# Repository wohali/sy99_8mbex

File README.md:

Yamaha SY99 8MB expansion board

v1.0 - Fabricated July/August 2018 - has issues, do not use

v1.1 - Fabricated September 2018 - all good!

Copyright 2018 Joan Sarah Touzet

License: CC BY-SA 3.0

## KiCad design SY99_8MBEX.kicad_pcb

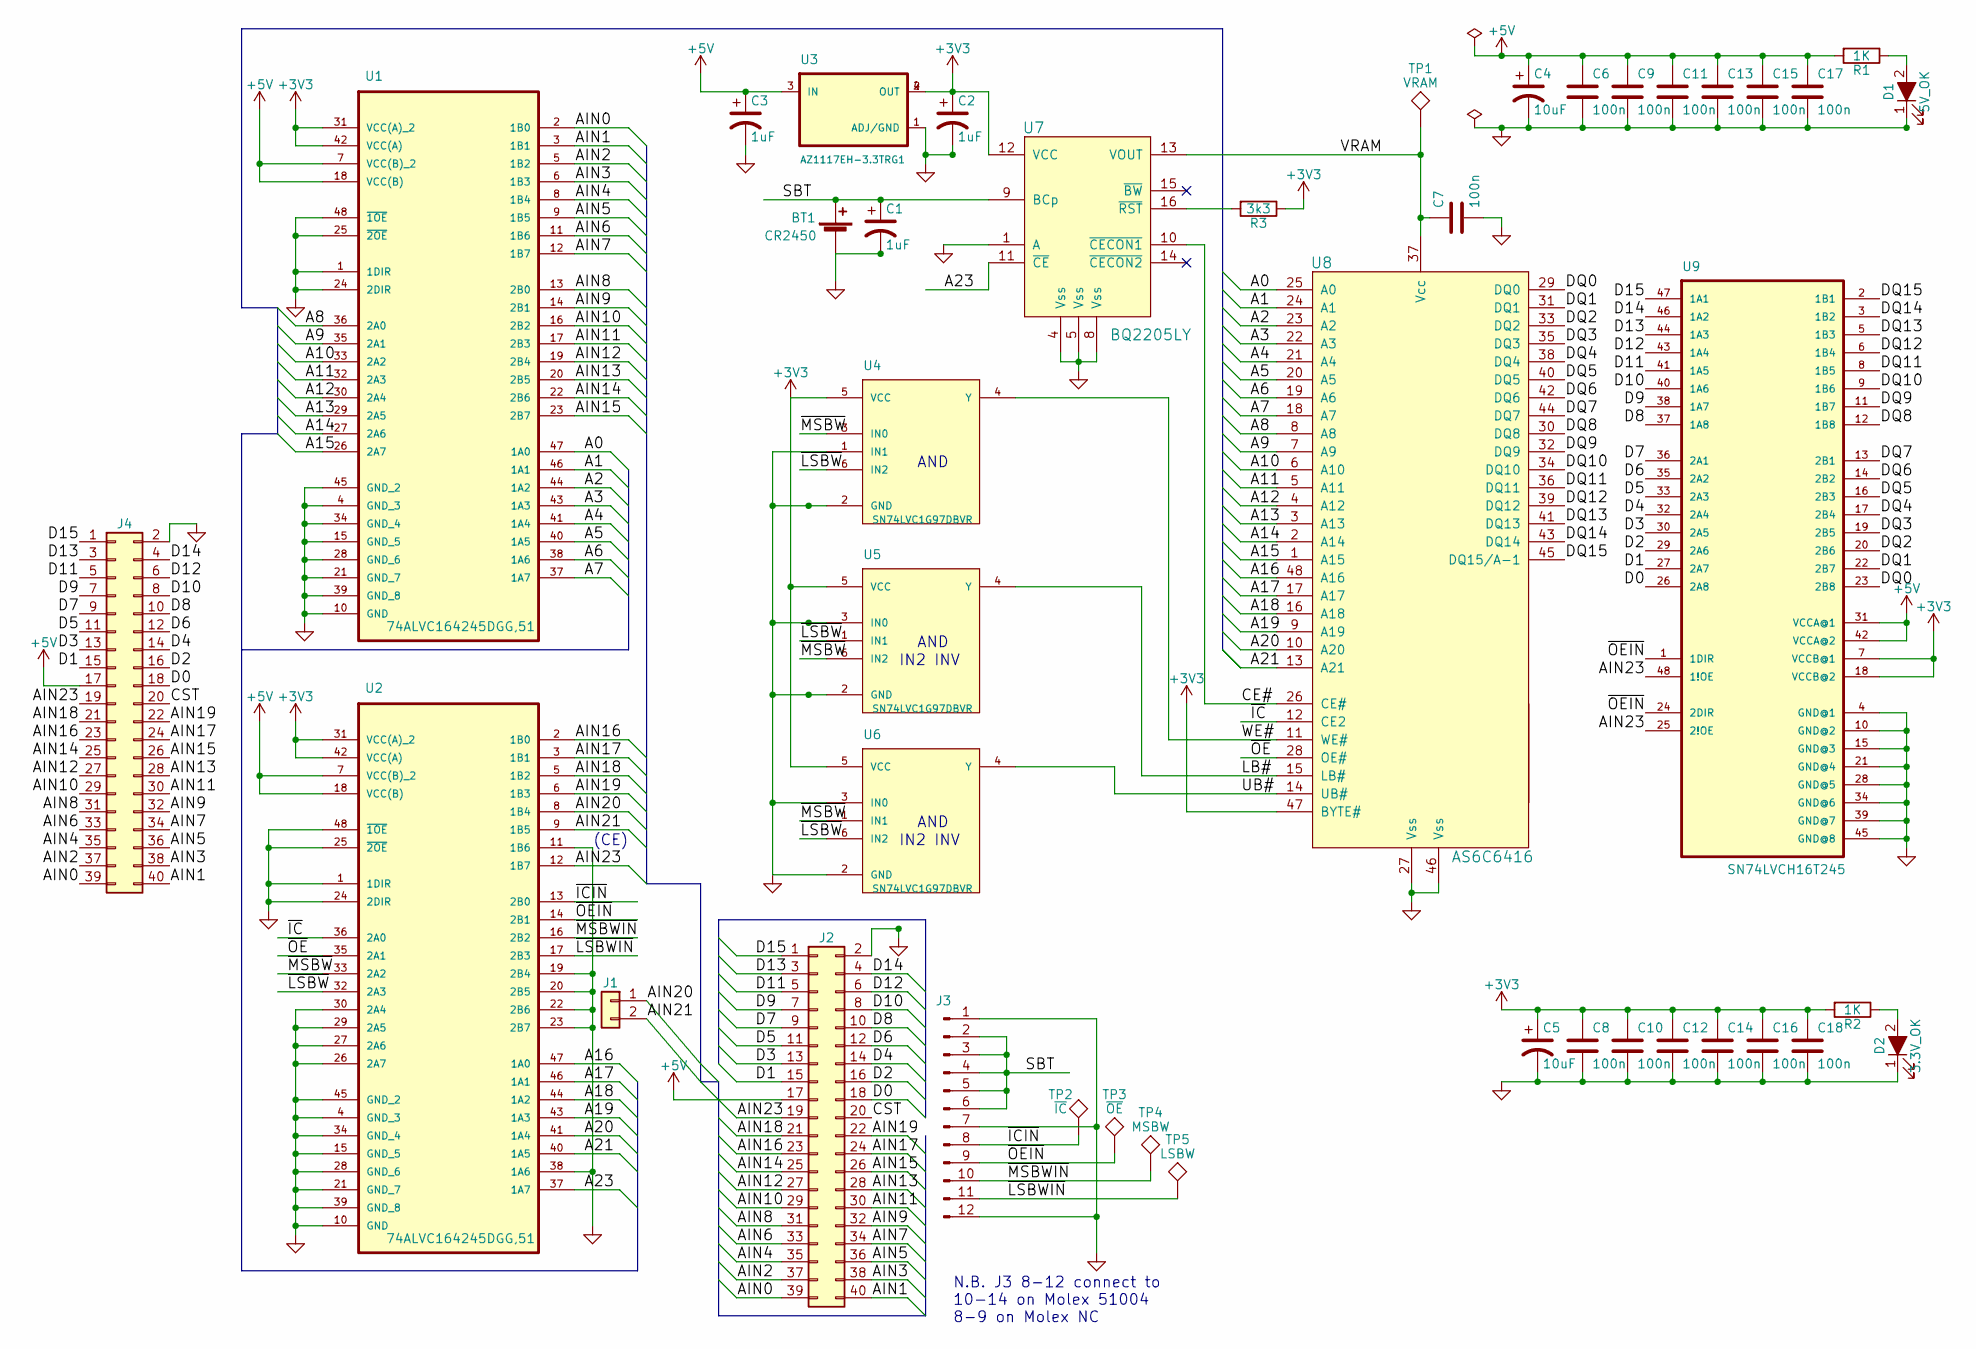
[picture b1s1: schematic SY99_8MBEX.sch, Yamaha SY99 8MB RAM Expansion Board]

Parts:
BT1: CR2450; Battery_Holder_Coin_2032_BS-7
C1, C2, C3: 1uF; CP_Tantalum_Case-A_EIA-3216-18_Reflow
C4, C5: 10uF; CP_Tantalum_Case-A_EIA-3216-18_Reflow
C6, C7, C8, C9, C10, C11, C12, C13, C14, C15, C16, C17, C18: 100n; C_0805_HandSoldering
D1: 5V_OK; LED_D5.0mm
D2: 3.3V_OK; LED_D5.0mm
J1: Conn_01x02; Pin_Header_Angled_1x02_Pitch2.54mm
J2: Conn_02x20_Odd_Even; Socket_Strip_Straight_2x20_Pitch2.54mm_10.30Wide_SMD
J3: Conn_01x12_Male; Pin_Header_Straight_1x12_Pitch2.54mm
J4: Conn_02x20_Odd_Even; Pin_Header_Straight_2x20_Pitch2.54mm_10.30Wide_SMD
R1, R2: 1K; R_0805_HandSoldering
R3: 3k3; R_0805_HandSoldering
TP1: VRAM; PINTST
TP2: ~IC; PINTST
TP3: ~OE; PINTST
TP4: MSBW; PINTST
TP5: LSBW; PINTST
U1, U2: 74ALVC164245DGG,51; SOP50P810X120-48N
U3: AZ1117EH-3.3TRG1; SOT230P700X180-4N
U4, U5, U6: SN74LVC1G97DBVR; SOT95P280X145-6N
U7: BQ2205LY; SOP65P640X120-16N
U8: AS6C6416; TSOP48
U9: SN74LVCH16T245; TSSOP48

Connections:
+3V3: C2.1, C5.1, C8.1, C10.1, C12.1, C14.1, C16.1, C18.1, R2.2, R3.1, U1.31 (VCC(A)_2), U1.42 (VCC(A)), U2.31 (VCC(A)_2), U2.42 (VCC(A)), U3.2 (OUT), U3.4 (OUT), U4.5 (VCC), U5.5 (VCC), U6.5 (VCC), U7.12 (VCC), U8.47 (BYTE#), U9.7 (VCCB@1), U9.18 (VCCB@2)
+5V: C3.1, C4.1, C6.1, C9.1, C11.1, C13.1, C15.1, C17.1, J2.17, J4.17, R1.2, U1.7 (VCC(B)_2), U1.18 (VCC(B)), U2.7 (VCC(B)_2), U2.18 (VCC(B)), U3.3 (IN), U9.31 (VCCA@1), U9.42 (VCCA@2)
/A0: U1.47 (1A0), U8.25 (A0)
/A1: U1.46 (1A1), U8.24 (A1)
/A2: U1.44 (1A2), U8.23 (A2)
/A3: U1.43 (1A3), U8.22 (A3)
/A4: U1.41 (1A4), U8.21 (A4)
/A5: U1.40 (1A5), U8.20 (A5)
/A6: U1.38 (1A6), U8.19 (A6)
/A7: U1.37 (1A7), U8.18 (A7)
/A8: U1.36 (2A0), U8.8 (A8)
/A9: U1.35 (2A1), U8.7 (A9)
/A10: U1.33 (2A2), U8.6 (A10)
/A11: U1.32 (2A3), U8.5 (A11)
/A12: U1.30 (2A4), U8.4 (A12)
/A13: U1.29 (2A5), U8.3 (A13)
/A14: U1.27 (2A6), U8.2 (A14)
/A15: U1.26 (2A7), U8.1 (A15)
/A16: U2.47 (1A0), U8.48 (A16)
/A17: U2.46 (1A1), U8.17 (A17)
/A18: U2.44 (1A2), U8.16 (A18)
/A19: U2.43 (1A3), U8.9 (A19)
/A20: U2.41 (1A4), U8.10 (A20)
/A21: U2.40 (1A5), U8.13 (A21)
/A23: U2.37 (1A7), U7.11 (~CE)
/AIN0: J2.39, J4.39, U1.2 (1B0)
/AIN1: J2.40, J4.40, U1.3 (1B1)
/AIN2: J2.37, J4.37, U1.5 (1B2)
/AIN3: J2.38, J4.38, U1.6 (1B3)
/AIN4: J2.35, J4.35, U1.8 (1B4)
/AIN5: J2.36, J4.36, U1.9 (1B5)
/AIN6: J2.33, J4.33, U1.11 (1B6)
/AIN7: J2.34, J4.34, U1.12 (1B7)
/AIN8: J2.31, J4.31, U1.13 (2B0)
/AIN9: J2.32, J4.32, U1.14 (2B1)
/AIN10: J2.29, J4.29, U1.16 (2B2)
/AIN11: J2.30, J4.30, U1.17 (2B3)
/AIN12: J2.27, J4.27, U1.19 (2B4)
/AIN13: J2.28, J4.28, U1.20 (2B5)
/AIN14: J2.25, J4.25, U1.22 (2B6)
/AIN15: J2.26, J4.26, U1.23 (2B7)
/AIN16: J2.23, J4.23, U2.2 (1B0)
/AIN17: J2.24, J4.24, U2.3 (1B1)
/AIN18: J2.21, J4.21, U2.5 (1B2)
/AIN19: J2.22, J4.22, U2.6 (1B3)
/AIN20: J1.1, U2.8 (1B4)
/AIN21: J1.2, U2.9 (1B5)
/AIN23: J2.19, J4.19, U2.12 (1B7), U9.25 (2!OE), U9.48 (1!OE)
/CE#: U7.10 (~CECON1), U8.26 (CE#)
/CST: J2.20, J4.20
/D0: J2.18, J4.18, U9.26 (2A8)
/D1: J2.15, J4.15, U9.27 (2A7)
/D2: J2.16, J4.16, U9.29 (2A6)
/D3: J2.13, J4.13, U9.30 (2A5)
/D4: J2.14, J4.14, U9.32 (2A4)
/D5: J2.11, J4.11, U9.33 (2A3)
/D6: J2.12, J4.12, U9.35 (2A2)
/D7: J2.9, J4.9, U9.36 (2A1)
/D8: J2.10, J4.10, U9.37 (1A8)
/D9: J2.7, J4.7, U9.38 (1A7)
/D10: J2.8, J4.8, U9.40 (1A6)
/D11: J2.5, J4.5, U9.41 (1A5)
/D12: J2.6, J4.6, U9.43 (1A4)
/D13: J2.3, J4.3, U9.44 (1A3)
/D14: J2.4, J4.4, U9.46 (1A2)
/D15: J2.1, J4.1, U9.47 (1A1)
/DQ0: U8.29 (DQ0), U9.23 (2B8)
/DQ1: U8.31 (DQ1), U9.22 (2B7)
/DQ2: U8.33 (DQ2), U9.20 (2B6)
/DQ3: U8.35 (DQ3), U9.19 (2B5)
/DQ4: U8.38 (DQ4), U9.17 (2B4)
/DQ5: U8.40 (DQ5), U9.16 (2B3)
/DQ6: U8.42 (DQ6), U9.14 (2B2)
/DQ7: U8.44 (DQ7), U9.13 (2B1)
/DQ8: U8.30 (DQ8), U9.12 (1B8)
/DQ9: U8.32 (DQ9), U9.11 (1B7)
/DQ10: U8.34 (DQ10), U9.9 (1B6)
/DQ11: U8.36 (DQ11), U9.8 (1B5)
/DQ12: U8.39 (DQ12), U9.6 (1B4)
/DQ13: U8.41 (DQ13), U9.5 (1B3)
/DQ14: U8.43 (DQ14), U9.3 (1B2)
/DQ15: U8.45 (DQ15/A-1), U9.2 (1B1)
/LB#: U5.4 (Y), U8.15 (LB#)
/SBT: BT1.1 (+), C1.1, J3.2, J3.3, J3.4, J3.5, J3.6, U7.9 (BCp)
/UB#: U6.4 (Y), U8.14 (UB#)
/VRAM: C7.1, TP1.1, U7.13 (VOUT), U8.37 (Vcc)
/WE#: U4.4 (Y), U8.11 (WE#)
/~IC: U2.36 (2A0), U8.12 (CE2)
/~ICIN: J3.8, TP2.1, U2.13 (2B0)
/~LSBW: U2.32 (2A3), U4.6 (IN2), U5.1 (IN1), U6.6 (IN2)
/~LSBWIN: J3.11, TP5.1, U2.17 (2B3)
/~MSBW: U2.33 (2A2), U4.3 (IN0), U5.6 (IN2), U6.1 (IN1)
/~MSBWIN: J3.10, TP4.1, U2.16 (2B2)
/~OE: U2.35 (2A1), U8.28 (OE#)
/~OEIN: J3.9, TP3.1, U2.14 (2B1), U9.1 (1DIR), U9.24 (2DIR)
GND: BT1.2 (-), C1.2, C2.2, C3.2, C4.2, C5.2, C6.2, C7.2, C8.2, C9.2, C10.2, C11.2, C12.2, C13.2, C14.2, C15.2, C16.2, C17.2, C18.2, D1.1 (K), D2.1 (K), J2.2, J3.1, J3.7, J3.12, J4.2, U1.1 (1DIR), U1.4 (GND_3), U1.10 (GND), U1.15 (GND_5), U1.21 (GND_7), U1.24 (2DIR), U1.25 (~2OE), U1.28 (GND_6), U1.34 (GND_4), U1.39 (GND_8), U1.45 (GND_2), U1.48 (~1OE), U2.1 (1DIR), U2.4 (GND_3), U2.10 (GND), U2.11 (1B6), U2.15 (GND_5), U2.19 (2B4), U2.20 (2B5), U2.21 (GND_7), U2.22 (2B6), U2.23 (2B7), U2.24 (2DIR), U2.25 (~2OE), U2.26 (2A7), U2.27 (2A6), U2.28 (GND_6), U2.29 (2A5), U2.30 (2A4), U2.34 (GND_4), U2.38 (1A6), U2.39 (GND_8), U2.45 (GND_2), U2.48 (~1OE), U3.1 (ADJ/GND), U4.1 (IN1), U4.2 (GND), U5.2 (GND), U5.3 (IN0), U6.2 (GND), U6.3 (IN0), U7.1 (A), U7.4 (Vss), U7.5 (Vss), U7.8 (Vss), U8.27 (Vss), U8.46 (Vss), U9.4 (GND@1), U9.10 (GND@2), U9.15 (GND@3), U9.21 (GND@4), U9.28 (GND@5), U9.34 (GND@6), U9.39 (GND@7), U9.45 (GND@8)
unnamed: D1.2 (A), R1.1
unnamed: D2.2 (A), R2.1
unnamed: R3.2, U7.16 (~RST)

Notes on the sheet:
(CE)
AND
IN2 INV
N.B. J3 8-12 connect to 10-14 on Molex 51004 8-9 on Molex NC

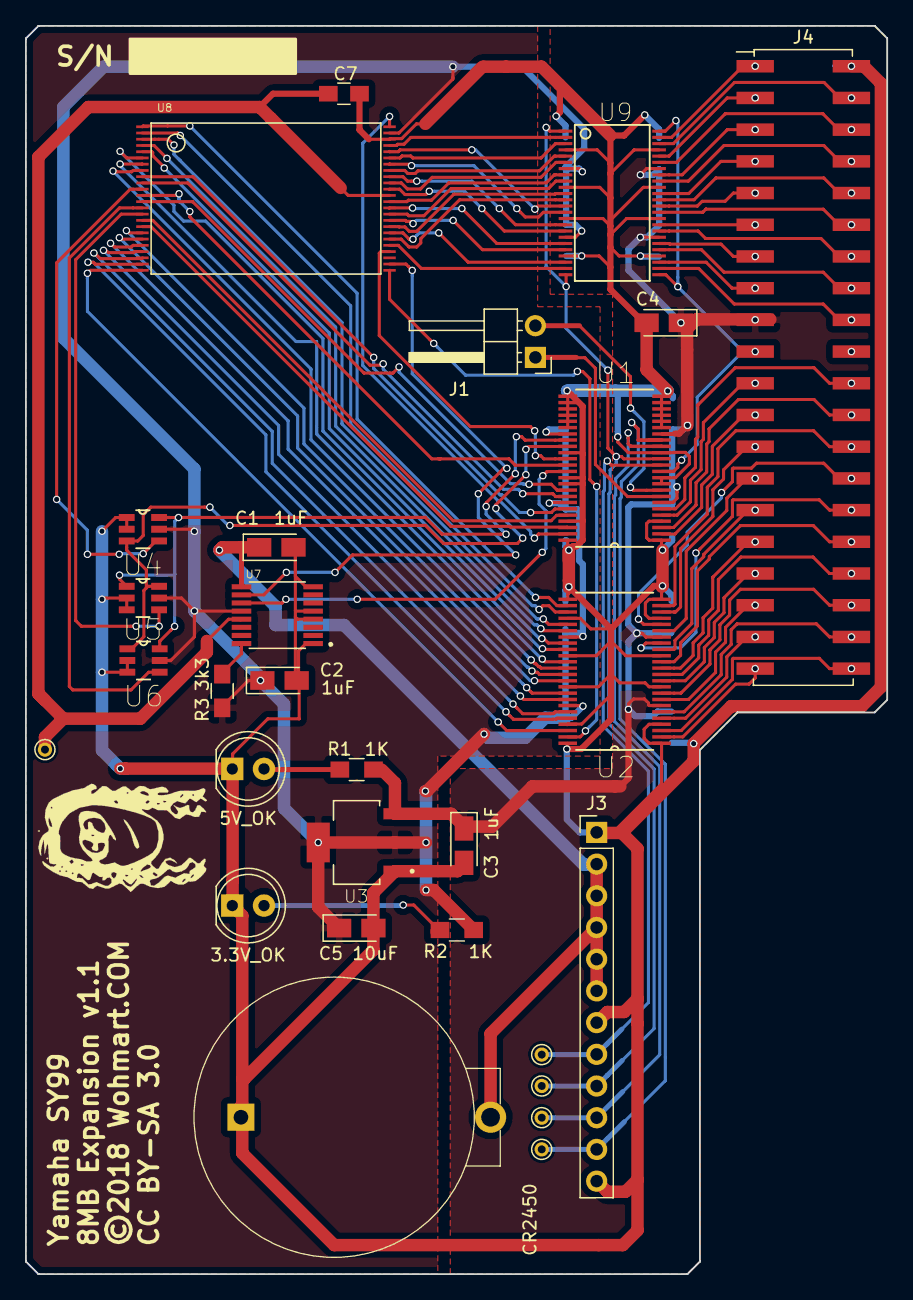
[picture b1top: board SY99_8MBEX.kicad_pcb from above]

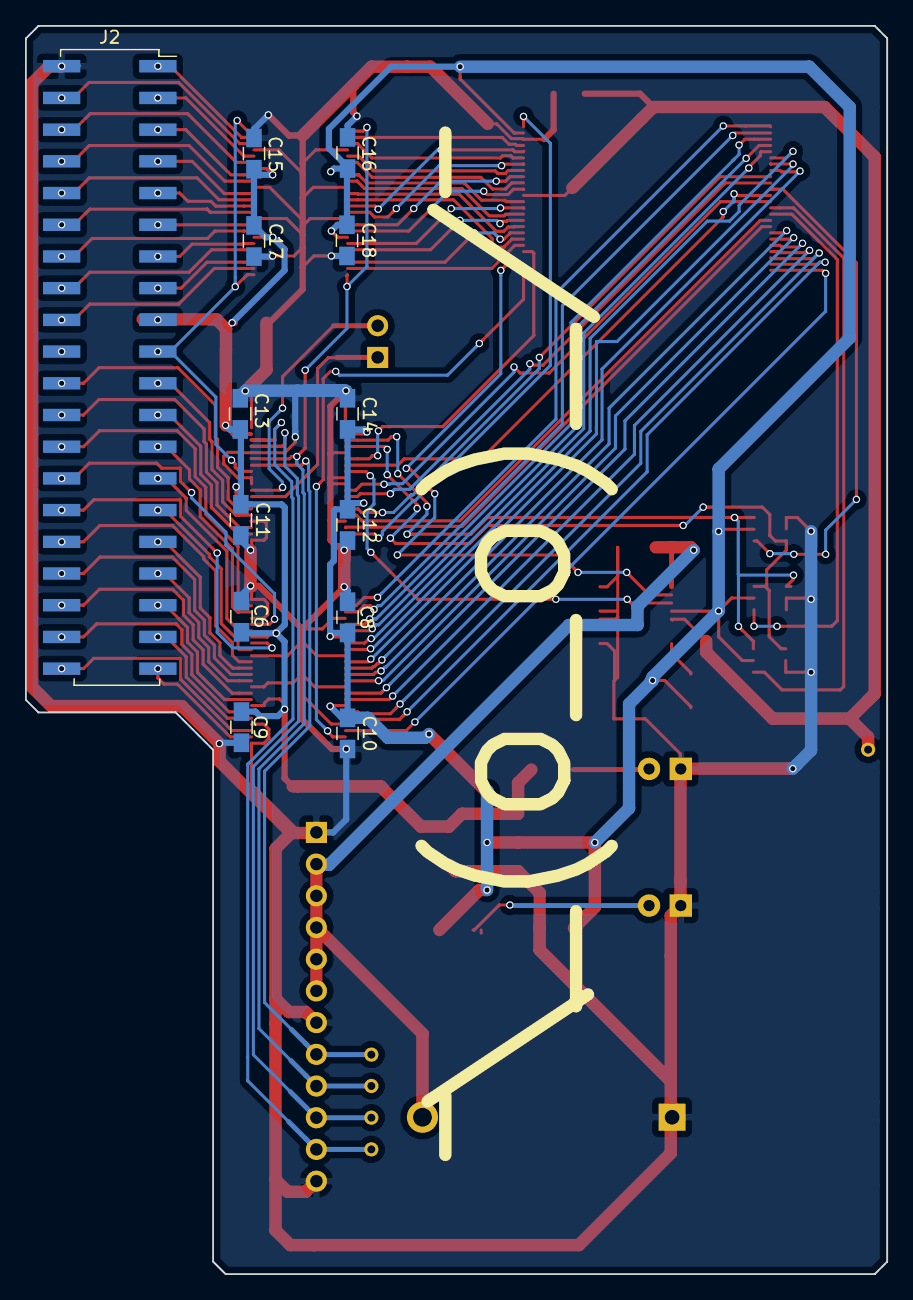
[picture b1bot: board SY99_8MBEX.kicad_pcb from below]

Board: 2 copper layers, 69.0 x 100.0 mm, 42 parts (13 on the bottom side), 99 nets.

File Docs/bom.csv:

Quantity,RefDes,Mfr Part No.,Digi-Key Part No.,Mouser Part No.,Description
1,BT1,1053,36-1053-ND,,"battery holder, CR2450"
3,"C1,C2,C3",T491A105K010AT ,399-9449-1-ND ,,"1uF tant cap 10V 10%, EIA 3216-18 (1206)"
2,"C4,C5",T491A106M010AT ,399-3686-1-ND ,,"10uF tant cap 10V 20%, EIA 3216-18 (1206)"
13,"C6,C7,C8,C9,C10,C11,C12,C13,C14,C15,C16,C17,C18",CL21F104ZAANNNC ,1276-1286-1-ND ,,"100nF cer cap 25V Y5V, 0805"
1,D1,,,,"5mm red LED, conventional"
1,D2,,,,"5mm green LED, conventional (not high-intensity)"
1,J1,640455-2 ,A19450-ND,,"Right angle 2 pin header, 2.54mm, tin"
1,J2,NPPC202KFMS-RC,S5734-ND,,"2x20 socket strip, SMD, 2.54mm, gold"
1,J3,1-640456-2 ,A19475-ND,,"MTA-100 1x12 pin header, vertical, keyed, tin"
1,J4,SBH11-NBPC-D20-SM-BK,S9192-ND,,"Pin header, 2x20, SMD, shrouded, 2.54mm, gold"
2,"R1,R2",ERJ-6GEYJ102V,P1.0KACT-ND ,,1k res 5% 0805
1,R3,CRCW08053K30FKEAC,541-4143-1-ND ,,3k3 res 1% 0805
2,"U1,U2","74ALVC164245DGG,11",1727-2771-ND,,"74ALVC16245 dual supply translating transceiver, TSSOP"
1,U3,AZ1117EH-3.3TRG1AZ1117EH-3.3TRG1DICT-ND,,"1A 3.3V linear regulator, SOT223"
3,"U4,U5,U6",SN74LVC1G97DBVR,296-15581-1-ND,,SN74LVC1G97 configurable multifunction gate
1,U7,BQ2205LYPWR,296-41203-1-ND,,"BQ2205LY SRAM supervisor, battery backup"
1,U8,AS6C6416-55TIN,1450-1464-ND,913-AS6C6416-55TIN ,"AS6C6416 8MB SRAM, parallel, TSOP I"
1,U9,SN74LVCH16T245DGGR,296-19568-1-ND,,"SN74LVCH16T245 dual supply translating transceiver, TSSOP"
,,,,,
1,,,WM18963-ND,,"Molex 51004-1400 MicroBlade housing, 14pos, 2.00mm"
12,,,WM18965CT-ND,,"Conn socket 24-30AWG crimp pin, tin"
1,,4-640441-2,A30941-ND ,,CONN RECEPT 12POS 24AWG MTA100
,,,,,
1,,,,,"PCB, custom"
1.6,,3050 VI005,A2015V-100-ND ,,"24AWG wire, in metres
100m spool == 53.39 --> 1.7516/m"
1,,,,,CR2450 battery 8.99/5 Amazon.ca
0.15,,,,,solder paste
0.05,,,,,flux pen
0.1,,59803-1 ,A9982-ND ,,T-HANDLE TOOL MTA-100

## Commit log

2018-08-28 Version 1.0
2018-08-28 Add README, LICENSE, cleanup
2018-09-15 Version 1.1
2018-09-15 Add missing BOM
2018-09-15 fix missing comma in bom

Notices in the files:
SY99_8MBEX.kicad_pcb:
©2018 Wohmart.COM
CC BY-SA 3.0
SY99_8MBEX.sch:
©2018 Joan Sarah Touzet
